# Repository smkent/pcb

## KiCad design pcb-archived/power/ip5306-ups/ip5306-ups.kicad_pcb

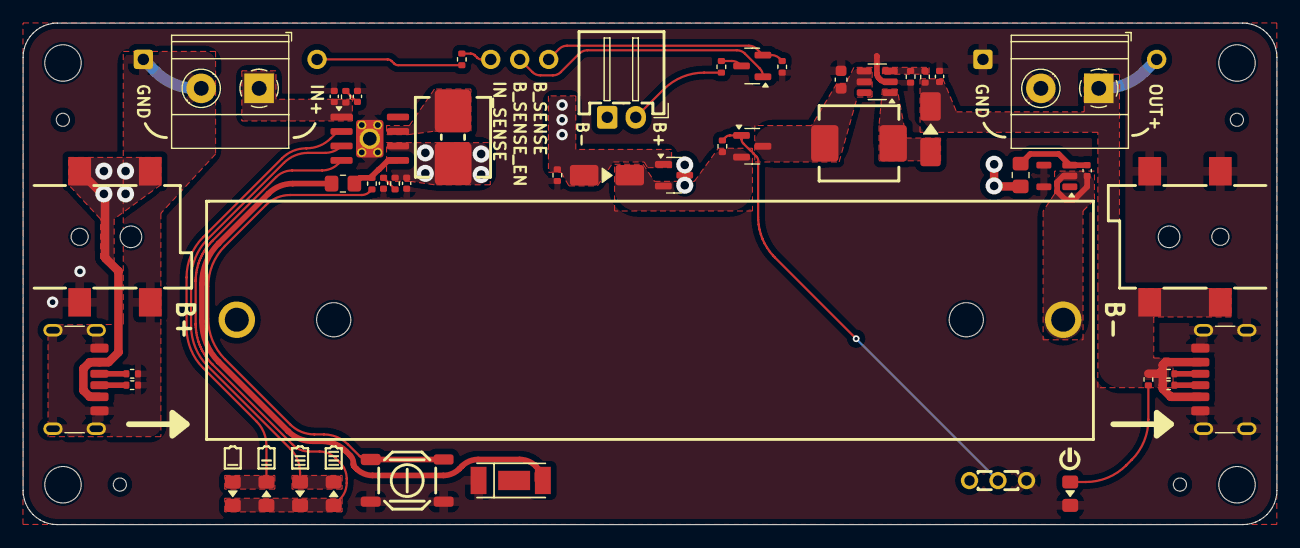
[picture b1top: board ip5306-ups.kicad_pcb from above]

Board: 2 copper layers, 110.0 x 44.0 mm, 55 parts (0 on the bottom side), 30 nets.

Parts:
BT1: Battery_Cell; BAT-TH_18650-A5BJ001
C1, C2, C6, C7, C11: 10uF; C_0402_1005Metric
C9: 0.1uF; C_0402_1005Metric
C10: 10uF; C_0603_1608Metric
D1, D2: SS34; D_SMA_simple
J1, J2: USB_C_Receptacle_PowerOnly_6P; USB_C_Receptacle_GCT_USB4125-xx-x_6P_TopMnt_Horizontal_hand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
J3, J6: Barrel_Jack_Switch; DC-IN_DC-050-2.0-BB
J4, J7: Screw_Terminal_01x02; TerminalBlock_Phoenix_MKDS-1,5-2-5.08_1x02_P5.08mm_Horizont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
J5, J8: Conn_01x01; PinHeader_1x01_P2.54mm_simple
J9: Conn_01x03; PinHeader_1x03_P2.54mm_Vertical_simple
J10: Conn_01x02; JST_XH_S2B-XH-2AW_1x02_P2.50mm_pad2gnd
J11, J12: Conn_01x01; PinHeader_1x01_P2.54mm_simple_square
L1: 1uH; Inductor_Multi_7.0x6.6_plus
L2: 22uH; IND-SMD_L7.0-W6.6
LED1, LED2, LED3, LED4: LED_0805_2012Metric_Pad1.15x1.40mm_HandSolder_simple
LED5: LED-SMD_3P-L5.7-W3.0-RD
LED6: Boost; LED_0805_2012Metric_Pad1.15x1.40mm_HandSolder_simple
Q1, Q2: AO3401A; SOT-23
Q3: AO3400A; SOT-23
R1, R6, R7, R9, R10, R15, R16, R17: 10K; R_0402_1005Metric
R2: 20R; R_0805_2012Metric_Pad1.20x1.40mm_HandSolder
R3, R4: 2R; R_0402_1005Metric
R5: 100R; R_0805_2012Metric_Pad1.20x1.40mm_HandSolder
R8: 75K; R_0402_1005Metric
R11, R12: 5K1; R_0402_1005Metric
R13, R14: 22K; R_0402_1005Metric
SW1: SW_Push; Push-Button-SMD-4x4x1.5mm_2P_Large_Pads
SW2: SW_SPDT; SW-TH_DEALON_SS-12D01-GX_simple
U1: IP5306; SOIC-8-1EP_3.9x4.9mm_P1.27mm_EP2.41x3.3mm_ThermalVias_Custo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
U2: XB5350D0; SOT-23-5_simple
U3: MT3608; SOT-23-6

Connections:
B+: BT1.1 (+), C2.1, J10.1, L1.2, Q1.3 (D), R4.1, R5.1, R15.1, U1.6 (BAT)
B-: BT1.2 (-), C9.1, J10.2, U2.2 (GND)
BATVDD: C9.2, R5.2, U2.3 (VDD)
BAT_SENSE: J9.1, Q3.2 (S), R16.1
BAT_SENSE_ENABLE: J9.2, Q3.1 (G)
BOOST: C10.1, L2.1, Q2.3 (D), U3.4 (EN), U3.5 (IN)
BOOST_SW: D2.2 (A), L2.2, U3.1 (SW)
FB: R8.2, R9.1, U3.3 (FB)
GND: C1.2, C2.2, C6.2, C7.2, C10.2, C11.2, J2.A12 (GND), J2.B12 (GND), J2.S1 (SHIELD), J3.2, J6.2, J6.3, J7.2, J12.1, LED5.1 (K), LED6.1 (K), R6.2, R9.2, R16.2, SW1.2, SW2.3 (C), U1.9 (EP), U2.4 (VM), U2.5 (VM), U3.2 (GND)
GND_PINS: J1.A12 (GND), J1.B12 (GND), J1.S1 (SHIELD), J3.3, J4.2, J11.1, R11.2, R12.2
KEY: R1.1, R2.1, U1.5 (KEY)
LED1: LED1.2 (A), LED2.1 (K), U1.2 (LED1)
LED2: LED3.2 (A), LED4.1 (K), U1.3 (LED2)
LED3: LED1.1 (K), LED2.2 (A), LED3.1 (K), LED4.2 (A), U1.4 (LED3)
LOAD_SWITCH: D1.1 (K), Q1.2 (S), Q2.2 (S), R7.1
unnamed: C6.1, R3.2
unnamed: C7.1, R4.2
unnamed: J1.A5 (CC1), R12.1
unnamed: J1.B5 (CC2), R11.1
unnamed: J2.A5 (CC1), R13.2
unnamed: J2.B5 (CC2), R14.2
unnamed: LED5.2 (A), R2.2
unnamed: LED6.2 (A), R10.2
unnamed: Q2.1 (G), R7.2, SW2.2 (B)
unnamed: Q3.3 (D), R15.2
unnamed: R1.2, SW1.1
POWER_IN_SENSE: J9.3, R17.2
SW: L1.1, U1.7 (SW)
VIN: C1.1, D1.2 (A), J1.A9 (VBUS), J1.B9 (VBUS), J3.1, J4.1, J5.1, Q1.1 (G), R3.1, R6.1, R17.1, U1.1 (VIN)
VOUT: C11.1, D2.1 (K), J2.A9 (VBUS), J2.B9 (VBUS), J6.1, J7.1, J8.1, R8.1, R10.1, R13.1, R14.1

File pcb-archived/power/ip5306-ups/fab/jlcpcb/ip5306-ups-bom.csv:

Comment,Designator,Footprint,LCSC
10K,"R1,R6,R7,R9,R10,R15,R16,R17",Resistor_SMD:R_0402_1005Metric,C25744
Battery_Cell,BT1,lcsc:BAT-TH_18650-A5BJ001,
Boost,LED6,custom:LED_0805_2012Metric_Pad1.15x1.40mm_HandSolder_simple,
AO3400A,Q3,Package_TO_SOT_SMD:SOT-23,
2R,"R3,R4",Resistor_SMD:R_0402_1005Metric,
~,"LED1,LED2,LED3,LED4",custom:LED_0805_2012Metric_Pad1.15x1.40mm_HandSolder_simple,
10uF,"C1,C2,C6,C7,C11",Capacitor_SMD:C_0402_1005Metric,C15525
20R,R2,Resistor_SMD:R_0805_2012Metric_Pad1.20x1.40mm_HandSolder,
IP5306,U1,custom:SOIC-8-1EP_3.9x4.9mm_P1.27mm_EP2.41x3.3mm_ThermalVias_CustomVias_Large,C181692
1uH,L1,custom:Inductor_Multi_7.0x6.6_plus,C5832376
SW_Push,SW1,custom:Push-Button-SMD-4x4x1.5mm_2P_Large_Pads,
~,LED5,lcsc:LED-SMD_3P-L5.7-W3.0-RD,
XB5350D0,U2,custom:SOT-23-5_simple,C2760002
100R,R5,Resistor_SMD:R_0805_2012Metric_Pad1.20x1.40mm_HandSolder,C17408
0.1uF,C9,Capacitor_SMD:C_0402_1005Metric,C1525
AO3401A,"Q1,Q2",Package_TO_SOT_SMD:SOT-23,C15127
SW_SPDT,SW2,custom:SW-TH_DEALON_SS-12D01-GX_simple,C2998803
SS34,"D1,D2",custom:D_SMA_simple,C8678
10uF,C10,Capacitor_SMD:C_0603_1608Metric,C19702
22uH,L2,lcsc:IND-SMD_L7.0-W6.6,C5832376
MT3608,U3,Package_TO_SOT_SMD:SOT-23-6,C84817
75K,R8,Resistor_SMD:R_0402_1005Metric,C25798
Conn_01x02,J10,custom:JST_XH_S2B-XH-2AW_1x02_P2.50mm_pad2gnd,
USB_C_Receptacle_PowerOnly_6P,J1,custom:USB_C_Receptacle_GCT_USB4125-xx-x_6P_TopMnt_Horizontal_handsolder,
Barrel_Jack_Switch,"J3,J6",custom:DC-IN_DC-050-2.0-BB,
Conn_01x01,"J11,J12",custom:PinHeader_1x01_P2.54mm_simple_square,
5K1,"R11,R12",Resistor_SMD:R_0402_1005Metric,C25905
22K,"R13,R14",Resistor_SMD:R_0402_1005Metric,C25768
Screw_Terminal_01x02,"J4,J7","custom:TerminalBlock_Phoenix_MKDS-1,5-2-5.08_1x02_P5.08mm_Horizontal",
USB_C_Receptacle_PowerOnly_6P,J2,custom:USB_C_Receptacle_GCT_USB4125-xx-x_6P_TopMnt_Horizontal_handsolder,
Conn_01x03,J9,custom:PinHeader_1x03_P2.54mm_Vertical_simple,
Conn_01x01,"J5,J8",custom:PinHeader_1x01_P2.54mm_simple,

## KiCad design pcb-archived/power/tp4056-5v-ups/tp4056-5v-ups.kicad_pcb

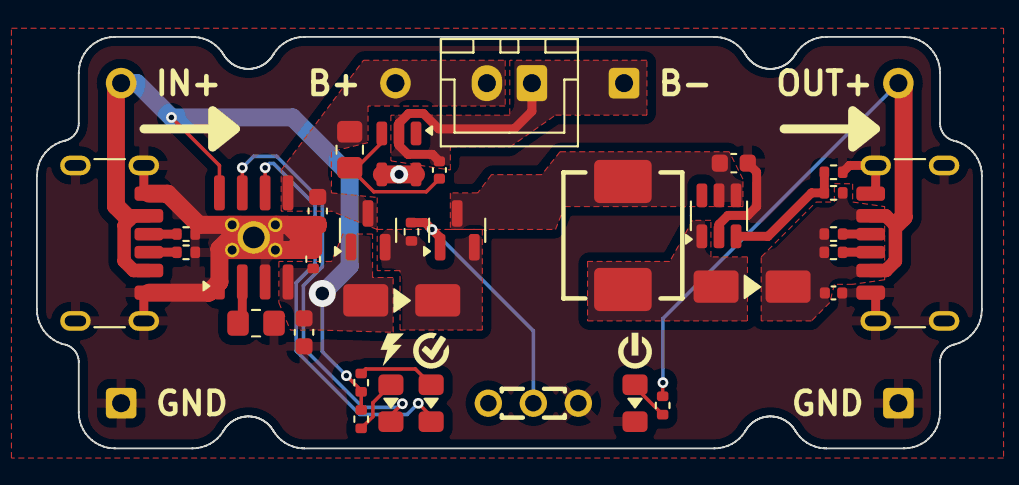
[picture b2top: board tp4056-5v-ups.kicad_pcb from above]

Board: 2 copper layers, 52.5 x 22.9 mm, 39 parts (0 on the bottom side), 21 nets.

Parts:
BT1: Battery_Cell; JST_XH_B2B-XH-A_1x02_P2.50mm_Vertical_simple_pad2gnd
C1, C2, C4: 10uF; C_0603_1608Metric
C3: 0.1uF; C_0402_1005Metric
C5: 10uF; C_0402_1005Metric
D1, D2: SS34; D_SMA_simple
J0, J1: USB_C_Receptacle_PowerOnly_6P; USB_C_Receptacle_GCT_USB4125-xx-x_6P_TopMnt_Horizontal_hand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
J101, J201, J301: Conn_01x01; PinHeader_1x01_P2.54mm_simple
J102, J202, J302: Conn_01x01; PinHeader_1x01_P2.54mm_simple_square
L1: 22uH; IND-SMD_L7.0-W6.6
LED1: Charge; LED_0805_2012Metric_Pad1.15x1.40mm_HandSolder_simple
LED2: Done; LED_0805_2012Metric_Pad1.15x1.40mm_HandSolder_simple
LED3: Boost; LED_0805_2012Metric_Pad1.15x1.40mm_HandSolder_simple
Q1, Q2: AO3401A; SOT-23
R1: 1K2; R_0805_2012Metric_Pad1.20x1.40mm_HandSolder
R2: 100R; R_0805_2012Metric_Pad1.20x1.40mm_HandSolder
R3: 75K; R_0402_1005Metric
R4, R5, R12, R13: 5K1; R_0402_1005Metric
R6, R7: 22K; R_0402_1005Metric
R8, R9, R10, R11: 10K; R_0402_1005Metric
SW1: SW_SPDT; SW-TH_DEALON_SS-12D01-GX_simple
U1: TP4056; SOIC-8-1EP_3.9x4.9mm_P1.27mm_EP2.41x3.3mm_ThermalVias_Custo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
U2: XB5350D0; SOT-23-5_simple
U3: MT3608; SOT-23-6

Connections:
B+: BT1.1 (+), C2.2, J301.1, Q1.3 (D), R2.1, U1.5 (BAT)
B-: BT1.2 (-), C3.1, J302.1, U2.2 (GND)
BATVDD: C3.2, R2.2, U2.3 (VDD)
BOOST: C4.1, L1.1, Q2.3 (D), U3.4 (EN), U3.5 (IN)
FB: R3.2, R10.1, U3.3 (FB)
GND: C1.2, C2.1, C4.2, C5.2, J0.A12 (GND), J0.B12 (GND), J0.S1 (SHIELD), J1.A12 (GND), J1.B12 (GND), J1.S1 (SHIELD), J102.1, J202.1, LED3.1 (K), R1.2, R4.2, R5.2, R10.2, R11.2, SW1.3 (C), U1.1 (TEMP), U1.3 (GND), U1.9 (EP), U2.4 (VM), U2.5 (VM), U3.2 (GND)
LOAD_SWITCH: D1.1 (K), Q1.2 (S), Q2.2 (S), R8.1
unnamed: J0.A5 (CC1), R5.1
unnamed: J0.B5 (CC2), R4.1
unnamed: J1.A5 (CC1), R7.2
unnamed: J1.B5 (CC2), R6.2
unnamed: LED1.2 (A), R12.2
unnamed: LED1.1 (K), U1.7 (~CHRG)
unnamed: LED2.2 (A), R13.2
unnamed: LED2.1 (K), U1.6 (~STDBY)
unnamed: LED3.2 (A), R9.2
unnamed: Q2.1 (G), R8.2, SW1.2 (B)
unnamed: R1.1, U1.2 (PROG)
SW: D2.2 (A), L1.2, U3.1 (SW)
VIN: C1.1, D1.2 (A), J0.A9 (VBUS), J0.B9 (VBUS), J101.1, Q1.1 (G), R11.1, R12.1, R13.1, U1.4 (VCC), U1.8 (CE)
VOUT: C5.1, D2.1 (K), J1.A9 (VBUS), J1.B9 (VBUS), J201.1, R3.1, R6.1, R7.1, R9.1

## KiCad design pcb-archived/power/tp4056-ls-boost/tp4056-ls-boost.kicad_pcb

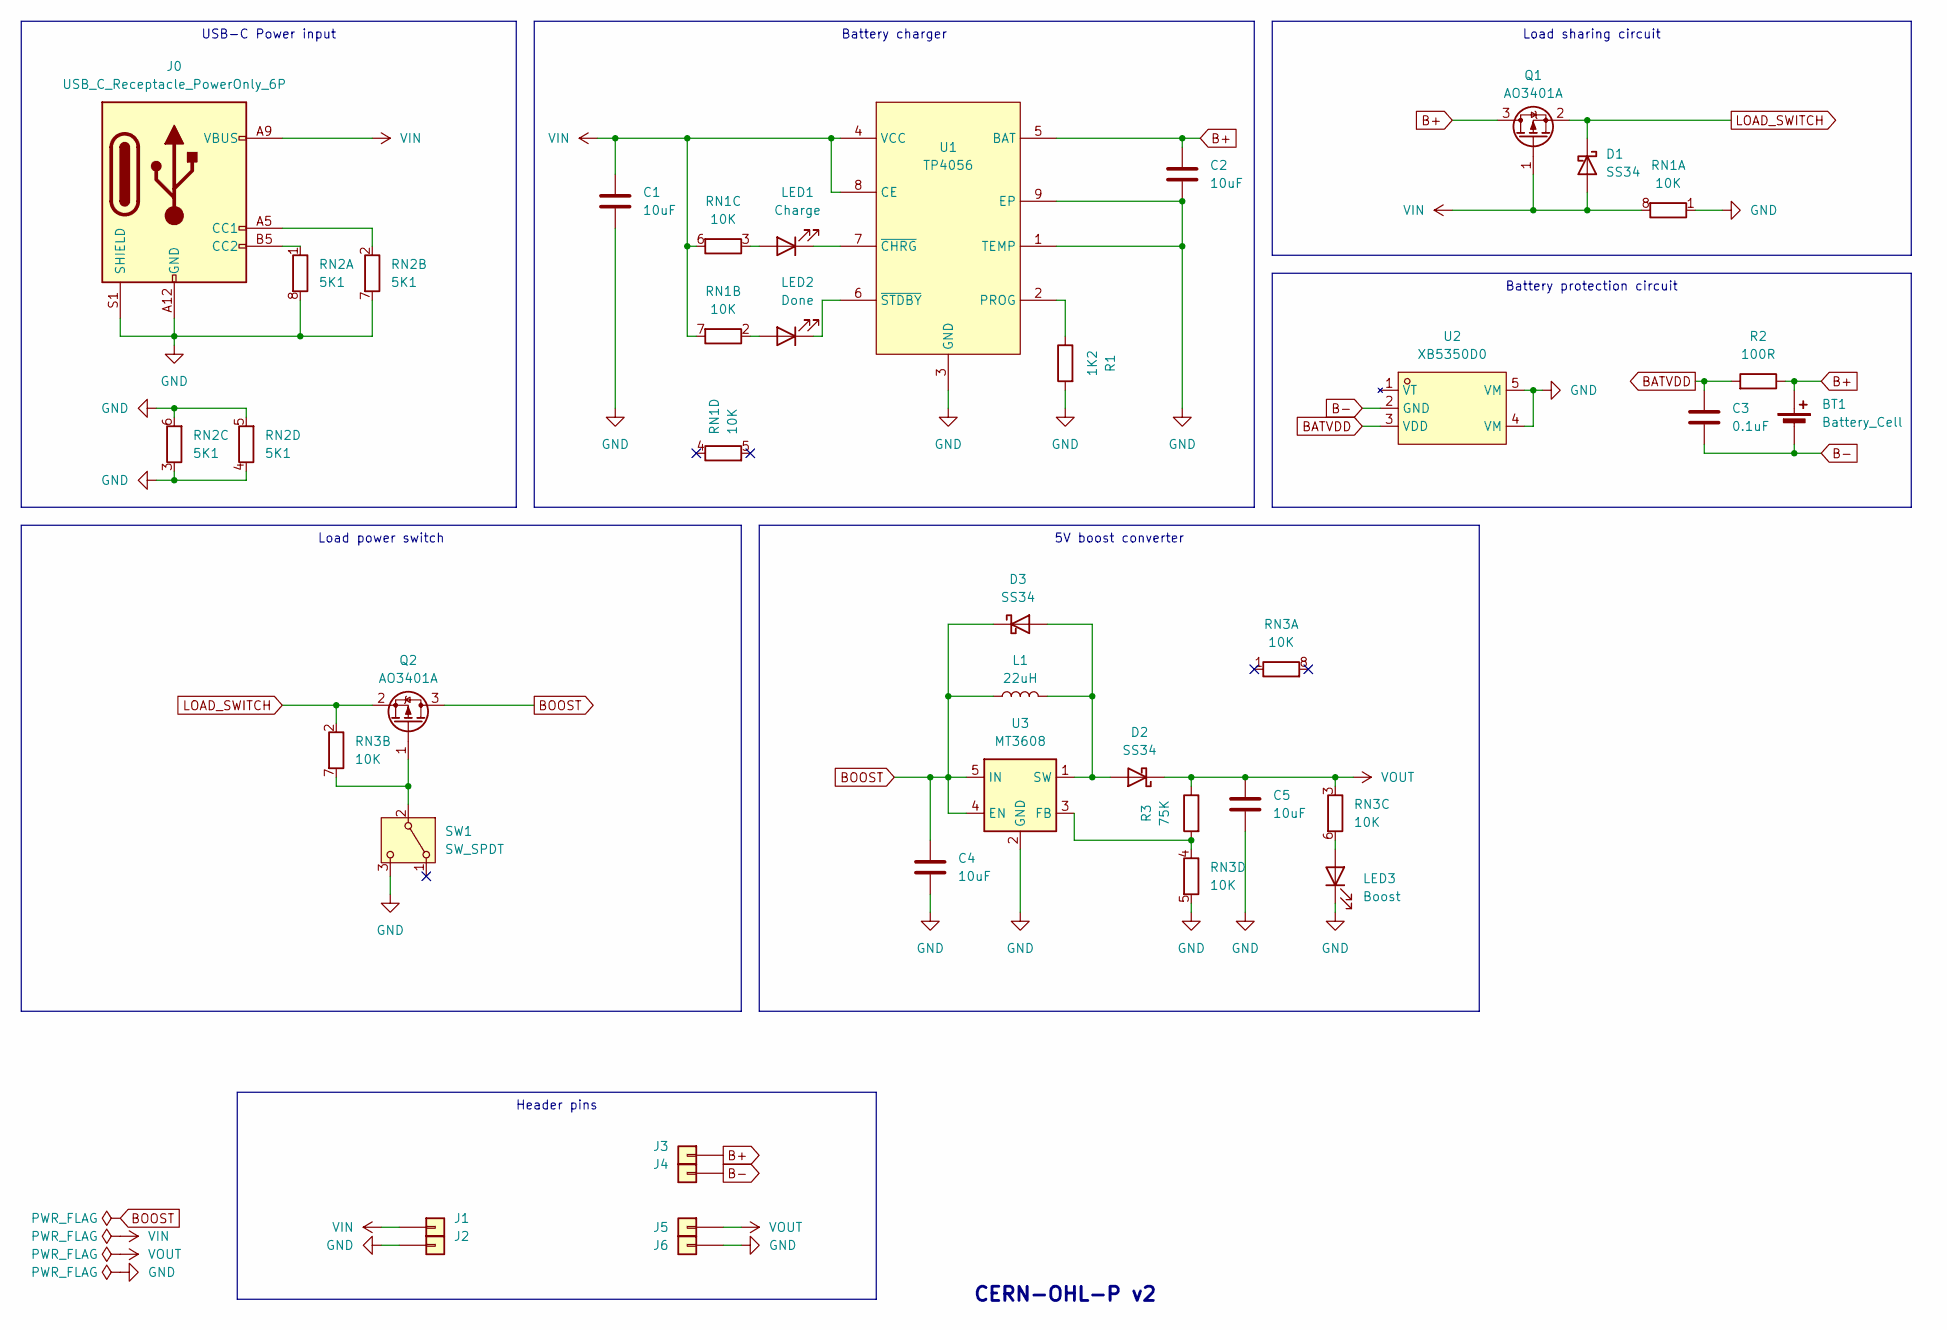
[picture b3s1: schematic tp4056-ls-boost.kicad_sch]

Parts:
BT1: Battery_Cell; JST_XH_B2B-XH-A_1x02_P2.50mm_Vertical_simple
C1, C2, C4, C5: 10uF; C_0805_2012Metric_Pad1.18x1.45mm_HandSolder; LCSC Part C15850
C3: 0.1uF; C_0805_2012Metric_Pad1.18x1.45mm_HandSolder; LCSC Part C28233
D1, D2, D3: SS34; D_SMA_simple; LCSC Part C8678
J0: USB_C_Receptacle_PowerOnly_6P; USB_C_Receptacle_GCT_USB4125-xx-x_6P_TopMnt_Horizontal_hand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
J1, J3, J5: Conn_01x01; PinHeader_1x01_P2.54mm_simple
J2, J4, J6: Conn_01x01; PinHeader_1x01_P2.54mm_simple_square
L1: 22uH; IND-SMD_L7.0-W6.6; LCSC Part C5832376
LED1: Charge; LED_0805_2012Metric_Pad1.15x1.40mm_HandSolder_simple
LED2: Done; LED_0805_2012Metric_Pad1.15x1.40mm_HandSolder_simple
LED3: Boost; LED_0805_2012Metric_Pad1.15x1.40mm_HandSolder_simple
Q1, Q2: AO3401A; SOT-23; LCSC Part C15127
R1: 1K2; R_0805_2012Metric_Pad1.20x1.40mm_HandSolder; LCSC Part C17379
R2: 100R; R_0805_2012Metric_Pad1.20x1.40mm_HandSolder; LCSC Part C17408
R3: 75K; R_0805_2012Metric_Pad1.20x1.40mm_HandSolder
RN1, RN3: 10K; R_Array_Convex_4x0603; LCSC Part C29718
RN2: 5K1; R_Array_Convex_4x0603
SW1: SW_SPDT; SW-TH_DEALON_SS-12D01-GX_simple; LCSC Part C2998803
U1: TP4056; SOIC-8-1EP_3.9x4.9mm_P1.27mm_EP2.41x3.3mm_ThermalVias_Custo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; JLCPCB_CORRECTION 0; 0; 270
U2: XB5350D0; SOT-23-5_simple; JLCPCB_CORRECTION 0; 0; 270
U3: MT3608; SOT-23-6; LCSC Part C84817

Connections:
B+: BT1.1 (+), C2.2, J3.1, Q1.3 (D), R2.1, U1.5 (BAT)
B-: BT1.2 (-), C3.1, J4.1, U2.2 (GND)
BATVDD: C3.2, R2.2, U2.3 (VDD)
BOOST: C4.1, D3.1 (K), L1.1, Q2.3 (D), U3.4 (EN), U3.5 (IN)
GND: C1.2, C2.1, C4.2, C5.2, J0.A12 (GND), J0.B12 (GND), J0.S1 (SHIELD), J2.1, J6.1, LED3.1 (K), R1.2, RN1.1 (R1.1), RN2.3 (R3.1), RN2.4 (R4.1), RN2.5 (R4.2), RN2.6 (R3.2), RN2.7 (R2.2), RN2.8 (R1.2), RN3.5 (R4.2), SW1.3 (C), U1.1 (TEMP), U1.3 (GND), U1.9 (EP), U2.4 (VM), U2.5 (VM), U3.2 (GND)
LOAD_SWITCH: D1.1 (K), Q1.2 (S), Q2.2 (S), RN3.2 (R2.1)
unnamed: D2.2 (A), D3.2 (A), L1.2, U3.1 (SW)
unnamed: J0.A5 (CC1), RN2.2 (R2.1)
unnamed: J0.B5 (CC2), RN2.1 (R1.1)
unnamed: LED1.2 (A), RN1.3 (R3.1)
unnamed: LED1.1 (K), U1.7 (~CHRG)
unnamed: LED2.2 (A), RN1.2 (R2.1)
unnamed: LED2.1 (K), U1.6 (~STDBY)
unnamed: LED3.2 (A), RN3.6 (R3.2)
unnamed: Q2.1 (G), RN3.7 (R2.2), SW1.2 (B)
unnamed: R3.2, RN3.4 (R4.1), U3.3 (FB)
unnamed: R1.1, U1.2 (PROG)
VIN: C1.1, D1.2 (A), J0.A9 (VBUS), J0.B9 (VBUS), J1.1, Q1.1 (G), RN1.6 (R3.2), RN1.7 (R2.2), RN1.8 (R1.2), U1.4 (VCC), U1.8 (CE)
VOUT: C5.1, D2.1 (K), J5.1, R3.1, RN3.3 (R3.1)

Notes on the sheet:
Header pins
Battery protection circuit
USB-C Power input
Load sharing circuit
Load power switch
Battery charger
5V boost converter
CERN-OHL-P v2

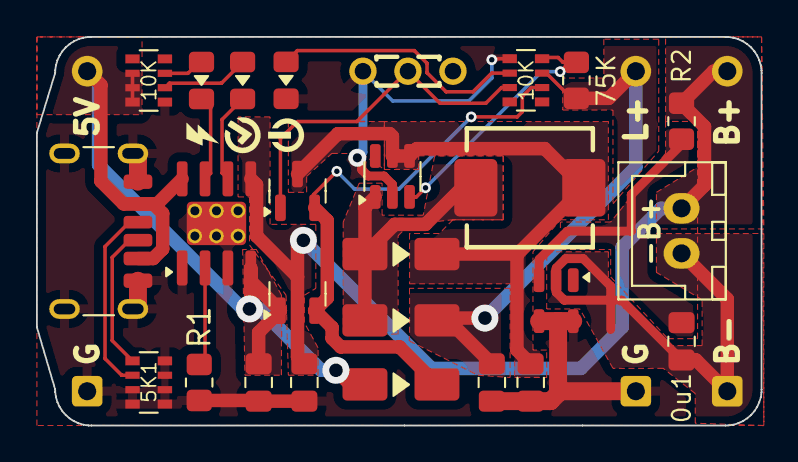
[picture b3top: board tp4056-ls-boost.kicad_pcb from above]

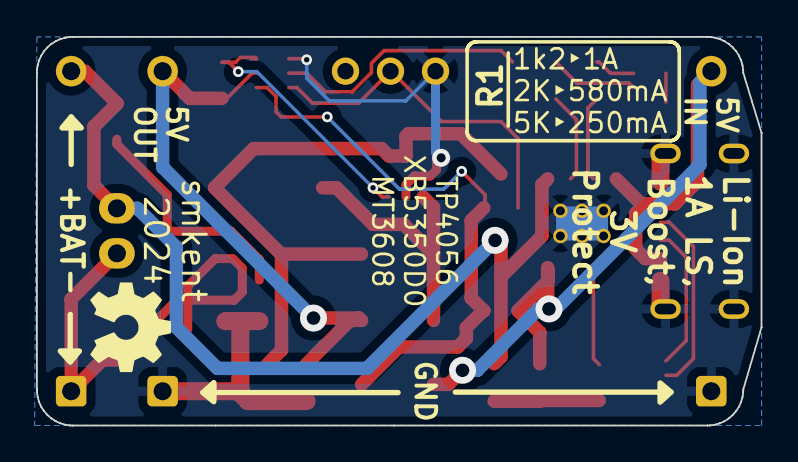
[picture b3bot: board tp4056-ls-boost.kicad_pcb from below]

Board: 2 copper layers, 40.3 x 21.6 mm, 32 parts (6 on the bottom side), 19 nets.

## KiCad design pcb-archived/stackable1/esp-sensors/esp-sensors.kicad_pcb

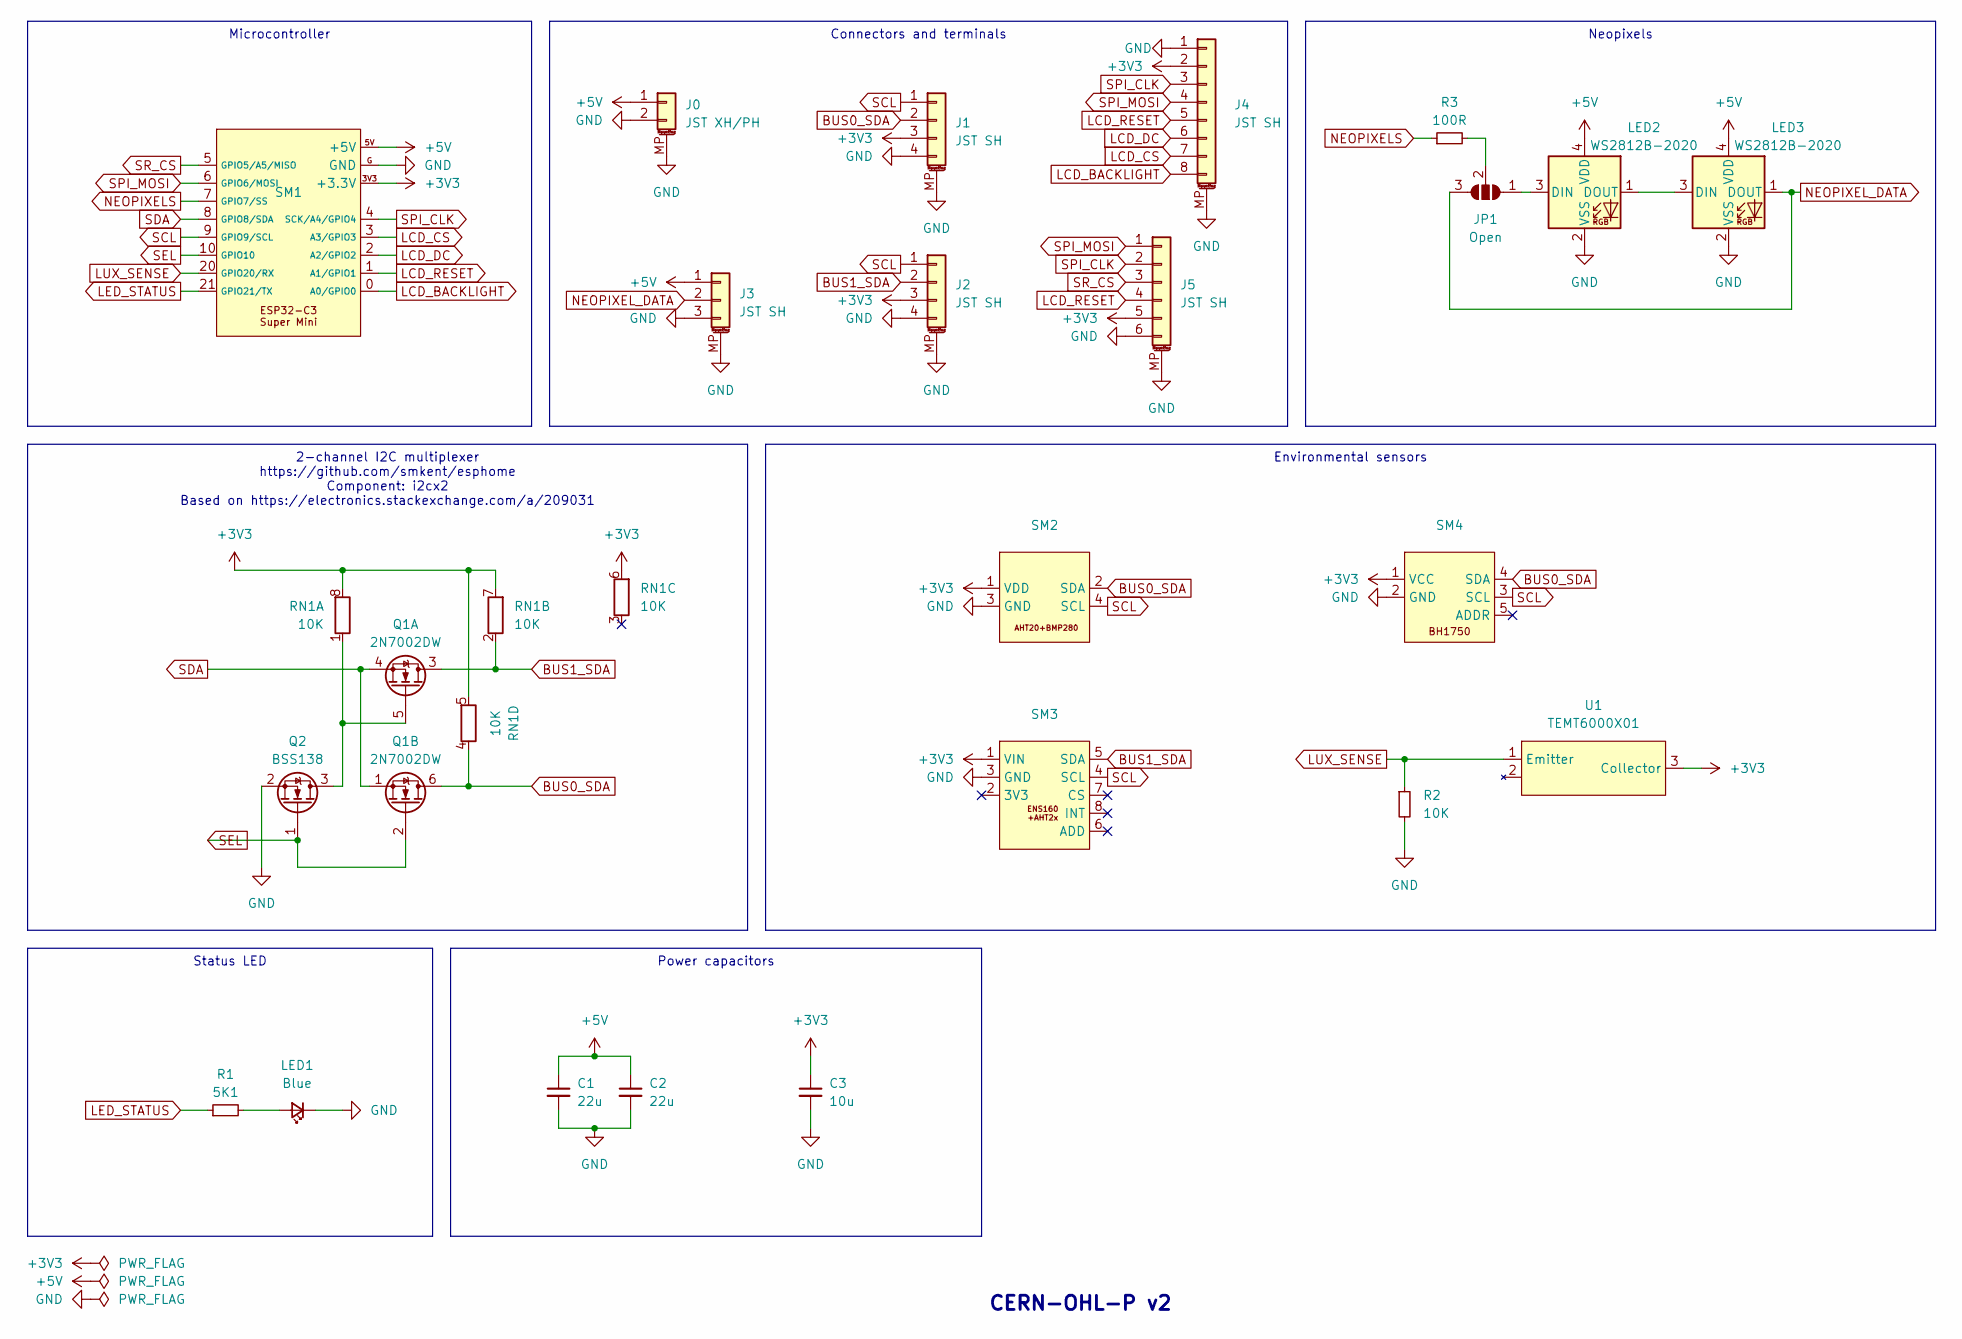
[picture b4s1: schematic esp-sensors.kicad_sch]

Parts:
C1, C2: 22u; C_0805_2012Metric_Pad1.18x1.45mm_HandSolder
C3: 10u; C_0603_1608Metric_Pad1.08x0.95mm_HandSolder
J0: JST XH/PH; Conn_Combo_JST-1x02-XH_PH-SMD-pad2gnd
J1, J2: JST SH; JST_SH_SM04B-SRSS-TB_1x04-1MP_P1.00mm_Horizontal
J3: JST SH; JST_SH_SM03B-SRSS-TB_1x03-1MP_P1.00mm_Horizontal
J4: JST SH; JST_SH_SM08B-SRSS-TB_1x08-1MP_P1.00mm_Horizontal
J5: JST SH; JST_SH_SM06B-SRSS-TB_1x06-1MP_P1.00mm_Horizontal
JP1: Open; SolderJumper-3_P1.3mm_Open_RoundedPad1.0x1.5mm
LED1: Blue; LED_0603_1608Metric_Pad1.05x0.95mm_HandSolder_simple
LED2, LED3: WS2812B-2020; LED-SMD_4P-L2.0-W2.0-BR-1
Q1: 2N7002DW; SOT-23-6; LCSC Part C5190214
Q2: BSS138; SOT-23
R1: 5K1; R_0603_1608Metric_Pad0.98x0.95mm_HandSolder_simple
R2: 10K; R_0603_1608Metric_Pad0.98x0.95mm_HandSolder_simple
R3: 100R; R_0603_1608Metric_Pad0.98x0.95mm_HandSolder
RN1: 10K; R_Array_Convex_4x0603
SM1: ESP32-C3-Super-Mini-Castellated-SMD
SM2: PinSocket_1x04_P2.54mm_Horizontal_descending_simple
SM3: PinSocket_1x08_P2.54mm_Horizontal_descending_simple
SM4: PinSocket_1x05_P2.54mm_Horizontal_simple
U1: TEMT6000X01; SENSORS-SMD_TEMT6000X01_HandSolder; LCSC Part C94098

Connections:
+3V3: C3.1, J1.3, J2.3, J4.2, J5.5, RN1.5 (R4.2), RN1.6 (R3.2), RN1.7 (R2.2), RN1.8 (R1.2), SM1.3V3 (+3.3V), SM2.1 (VDD), SM3.1 (VIN), SM4.1 (VCC), U1.3 (Collector)
+5V: C1.1, C2.1, J0.1, J3.1, LED2.4 (VDD), LED3.4 (VDD), SM1.5V (+5V)
BUS0_SDA: J1.2, Q1.6 (D), RN1.4 (R4.1), SM2.2 (SDA), SM4.4 (SDA)
BUS1_SDA: J2.2, Q1.3 (D), RN1.2 (R2.1), SM3.5 (SDA)
GND: C1.2, C2.2, C3.2, J0.2, J0.MP (MountPin), J1.4, J1.MP (MountPin), J2.4, J2.MP (MountPin), J3.3, J3.MP (MountPin), J4.1, J4.MP (MountPin), J5.6, J5.MP (MountPin), LED1.1 (K), LED2.2 (VSS), LED3.2 (VSS), Q2.2 (S), R2.2, SM1.G (GND), SM2.3 (GND), SM3.3 (GND), SM4.2 (GND)
LCD_BACKLIGHT: J4.8, SM1.0 (A0/GPIO0)
LCD_CS: J4.7, SM1.3 (A3/GPIO3)
LCD_DC: J4.6, SM1.2 (A2/GPIO2)
LCD_RESET: J4.5, J5.4, SM1.1 (A1/GPIO1)
LED_STATUS: R1.1, SM1.21 (GPIO21/TX)
LUX_SENSE: R2.1, SM1.20 (GPIO20/RX), U1.1 (Emitter)
NEOPIXELS: R3.1, SM1.7 (GPIO7/SS)
NEOPIXEL_DATA: J3.2, JP1.3 (B), LED3.1 (DOUT)
unnamed: JP1.1 (A), LED2.3 (DIN)
unnamed: JP1.2 (C), R3.2
unnamed: LED1.2 (A), R1.2
unnamed: LED2.1 (DOUT), LED3.3 (DIN)
unnamed: Q1.5 (G), Q2.3 (D), RN1.1 (R1.1)
SCL: J1.1, J2.1, SM1.9 (GPIO9/SCL), SM2.4 (SCL), SM3.4 (SCL), SM4.3 (SCL)
SDA: Q1.1 (S), Q1.4 (S), SM1.8 (GPIO8/SDA)
SEL: Q1.2 (G), Q2.1 (G), SM1.10 (GPIO10)
SPI_CLK: J4.3, J5.2, SM1.4 (SCK/A4/GPIO4)
SPI_MOSI: J4.4, J5.1, SM1.6 (GPIO6/MOSI)
SR_CS: J5.3, SM1.5 (GPIO5/A5/MISO)

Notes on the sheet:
2-channel I2C multiplexer https://github.com/smkent/esphome Component: i2cx2 Based on https://electronics.stackexchange.com/a/209031
Environmental sensors
Microcontroller
Power capacitors
Neopixels
Status LED
Connectors and terminals
CERN-OHL-P v2

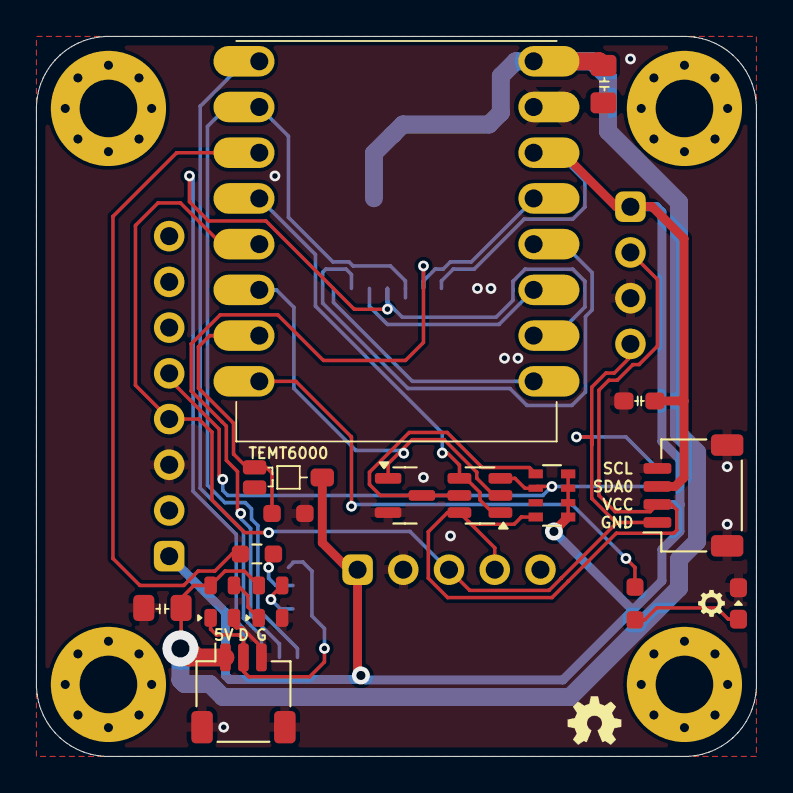
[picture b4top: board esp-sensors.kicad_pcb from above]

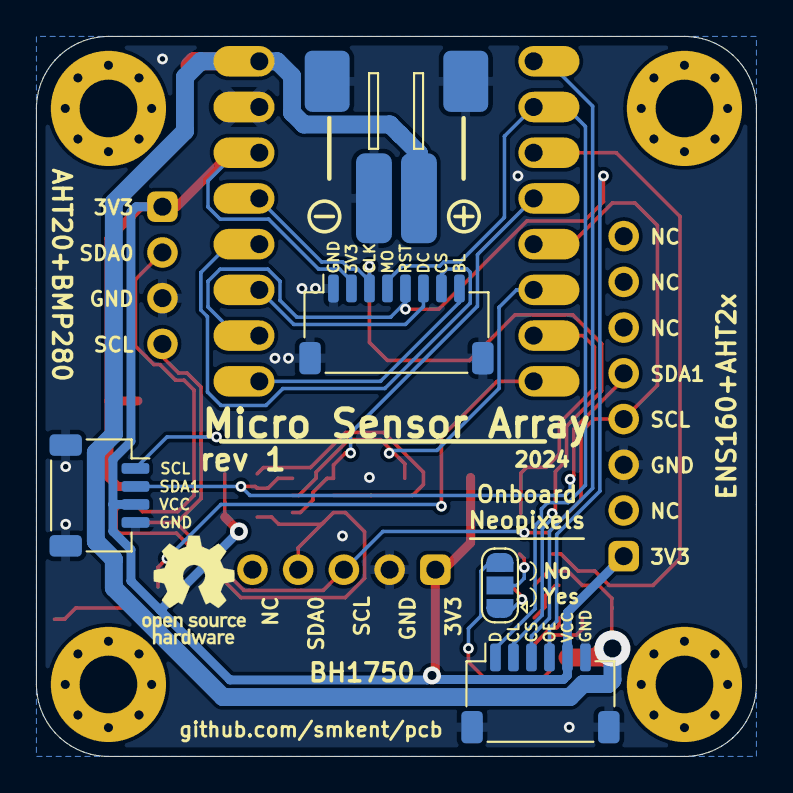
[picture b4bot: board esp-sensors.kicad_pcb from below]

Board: 2 copper layers, 40.0 x 40.0 mm, 24 parts (5 on the bottom side), 24 nets.

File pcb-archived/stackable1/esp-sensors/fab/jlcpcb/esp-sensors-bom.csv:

Comment,Designator,Footprint,LCSC
22u,"C1,C2",custom:C_0805_2012Metric_Pad1.18x1.45mm_HandSolder,
100R,R3,Resistor_SMD:R_0603_1608Metric_Pad0.98x0.95mm_HandSolder,
~,SM1,modules:ESP32-C3-Super-Mini-Castellated-SMD,
~,SM3,custom:PinSocket_1x08_P2.54mm_Horizontal_descending_simple,
5K1,R1,custom:R_0603_1608Metric_Pad0.98x0.95mm_HandSolder_simple,
WS2812B-2020,"LED2,LED3",lcsc:LED-SMD_4P-L2.0-W2.0-BR-1,
JST SH,"J1,J2",connectors:JST_SH_SM04B-SRSS-TB_1x04-1MP_P1.00mm_Horizontal,
Blue,LED1,custom:LED_0603_1608Metric_Pad1.05x0.95mm_HandSolder_simple,
JST SH,J4,connectors:JST_SH_SM08B-SRSS-TB_1x08-1MP_P1.00mm_Horizontal,
JST SH,J3,connectors:JST_SH_SM03B-SRSS-TB_1x03-1MP_P1.00mm_Horizontal,
JST XH/PH,J0,custom:Conn_Combo_JST-1x02-XH_PH-SMD-pad2gnd,
10K,R2,custom:R_0603_1608Metric_Pad0.98x0.95mm_HandSolder_simple,
10K,RN1,Resistor_SMD:R_Array_Convex_4x0603,
~,SM4,custom:PinSocket_1x05_P2.54mm_Horizontal_simple,
~,SM2,custom:PinSocket_1x04_P2.54mm_Horizontal_descending_simple,
2N7002DW,Q1,Package_TO_SOT_SMD:SOT-23-6,C5190214
TEMT6000X01,U1,custom:SENSORS-SMD_TEMT6000X01_HandSolder,C94098
BSS138,Q2,Package_TO_SOT_SMD:SOT-23,
10u,C3,custom:C_0603_1608Metric_Pad1.08x0.95mm_HandSolder,
JST SH,J5,connectors:JST_SH_SM06B-SRSS-TB_1x06-1MP_P1.00mm_Horizontal,

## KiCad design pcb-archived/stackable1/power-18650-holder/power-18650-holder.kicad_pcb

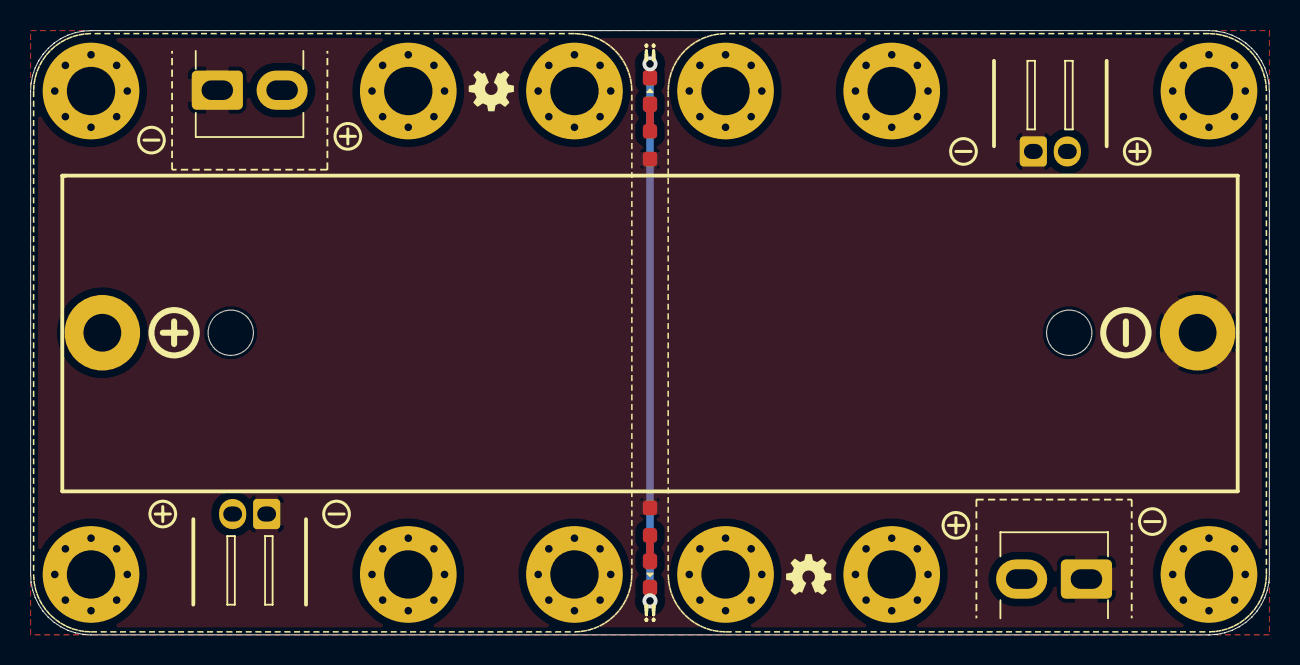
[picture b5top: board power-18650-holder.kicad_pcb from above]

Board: 2 copper layers, 82.0 x 40.0 mm, 9 parts (0 on the bottom side), 4 nets.

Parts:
BT1: Battery_Cell; BAT-TH_18650-A5BJ001_large_vias
J1, J2: JST XH/PH; Conn_Combo_JST-1x02-XH_PH-THT-pad2gnd
J3, J4: Screw_Terminal_01x02; Conn_Combo_TerminalBlock_P3.5-P5.08_1x02_pad2gnd
LED1, LED2: Red; LED_0603_1608Metric_Pad1.05x0.95mm_HandSolder_simple
R1, R2: 5K1; R_0603_1608Metric_Pad0.98x0.95mm_HandSolder_simple

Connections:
B+: BT1.1 (+), J1.1, J2.1, J3.1, J4.1, LED1.1 (K), LED2.1 (K)
B-: BT1.2 (-), J1.2, J2.2, J3.2, J4.2, R1.2, R2.2
unnamed: LED1.2 (A), R1.1
unnamed: LED2.2 (A), R2.1
